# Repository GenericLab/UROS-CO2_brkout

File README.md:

# UROS-CO2_brkout
## UROŠ - Breakout board for the Sensirion SCD41 CO2 sensor. 

**UROŠ - Ubiquitous Rural Open Science Hardware**, is a collaborative, regional and globally connected research project bringing together people from the Hackteria network, the global GOSH and preparing regional activities in Maribor, Slovenia. It is supported through the kons-platform.

More info on UROŠ on the hackteria wiki: https://www.hackteria.org/wiki/UROS

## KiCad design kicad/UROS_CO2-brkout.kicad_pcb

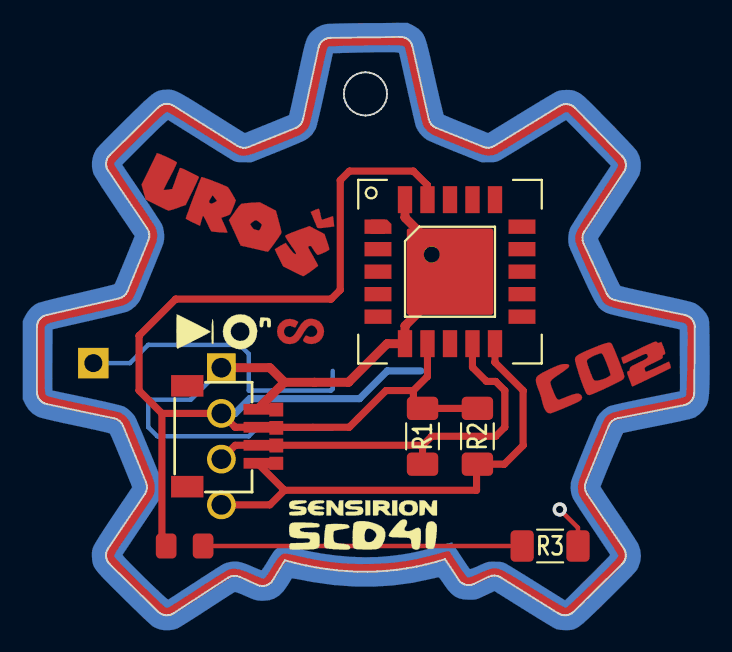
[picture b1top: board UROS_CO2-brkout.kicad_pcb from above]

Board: 2 copper layers, 36.6 x 32.1 mm, 12 parts (1 on the bottom side), 6 nets.

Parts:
Board1: EdgeCut; UROS_SCD41_edge
Board2: Front; UROS_SCD41_frontLogos
Board3: Back; UROS_SCD41_backside
CONN1: Adafruit_SCD-41-eagle-import_STEMMA_I2C_QT; JST_SH4_3D
D1: LED; LED_0805_HandSolder
D2: WS2812B; NEO-Pixel_WS2812B
J2: Conn_01x04; HEADER-4P_new
J3: Conn_01x01; PinHeader_1x01
R1, R2, R3: 10k; R_1206_HandSolder
U1: SCD41; SCD41_3D

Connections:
GND: Board2.1, CONN1.1, D2.3, J2.1, R3.2, U1.6, U1.20, U1.21
NEO_IN: D2.4, J3.1
unnamed: D1.1, R3.1
SCL: CONN1.3, J2.3, R1.1, U1.9
SDA: CONN1.4, J2.4, R2.1, U1.10
VCC: CONN1.2, D1.2, D2.1, J2.2, R1.2, R2.2, U1.7, U1.19
